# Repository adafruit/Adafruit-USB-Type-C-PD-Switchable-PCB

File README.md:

## Adafruit USB Type C Power Delivery Dummy - I2C or Switchable - HUSB238 - STEMMA QT / Qwiic PCB

<a href="http://www.adafruit.com/products/5991"><br/>
Click here to purchase one from the Adafruit shop</a>

PCB files for the Adafruit USB Type C Power Delivery Dummy - I2C or Switchable - HUSB238 - STEMMA QT / Qwiic. 

Format is EagleCAD schematic and board layout
* https://www.adafruit.com/product/5991

### Description

The HUSB238 USB PD sink chip is neat in that you can either use switches (really, resistor selection) to set the desired PD voltage or use I2C for dynamic querying and setting. We already stock a simple Adafruit USB Type C Power Delivery Dummy Breakout board around the HUSB238, but that one requires soldering closed jumpers to select the voltage. For folks who want a no-soldering-required board, this Adafruit USB Type C Power Delivery Dummy - I2C or Switchable is ready for instant gratification. No soldering required!

Compared to the basic Adafruit USB Type C Power Delivery Dummy Breakout we've done a renovation to keep the same great schematic and also add some oft-requested features:

* No soldering required! Switches allow on-the-fly voltage changes. Terminal block can be used to provide power to your robot, display, LEDs, etc.
* Green LED output lets you know that the terminal block power is on - can be disabled if you prefer
* Stemma QT for I2C control plug-and-play with Qwiic/QT
* USB Data lines available on solderable pads
* On/Off switch - you can disconnect the internal pass FET by connecting a switch between two onboard pads. When the switch is closed the output will disconnect / turn off.
* We use the HUSB328 PDL003A E-Marker variant of the chip, a little more expensive, but it can request 5A power.

It's perfect for USB Type C wall adapters providing multiple voltages. The standard offerings are 5V, 9V, 12V, 15V, 18V, and 20V. This HUSB238 breakout plugs into the USB C cable and negotiates the PD request and commands over the CC lines. For example, we can ask what voltages are available and pick the highest. Or if you need a specific voltage, it will select that one.

This breakout will be handy for projects where you need a lot more than 5V @ 2A power: this adapter can give up to 20V at 5A - yes you can get 100W over USB C! - and you could buck that down to get a ton of current at 5V or 12V if that's needed. Or use it to convert a DC or battery-powered device into a USB C powered one!

DIP switch-configured usage is simple: simply unplug the USB PD so you don't accidentally select too high a voltage for your device. Then switch ON the voltage you want: 5V, 9V, 12V, 15V, 18V, or 20V. You'll get that voltage and as much current as the adapter will provide. No microcontroller or microcomputer is required!

I2C-configured usage is also available via a Stemma QT port. Use the Arduino library and example code to query the USB Type C PD source for available voltages and currents and select the desired voltage dynamically. When configuring over I2C, the jumper settings are used on startup until the I2C commands come over.

The STEMMA QT connector lets you make solderless connections between your development board and the breakout or chain it with a wide range of other sensors and accessories using a compatible cable. QT Cable is not included, but we have a variety in the shop. 

### License

Adafruit invests time and resources providing this open source design, please support Adafruit and open-source hardware by purchasing products from [Adafruit](https://www.adafruit.com)!

Designed by Limor Fried/Ladyada for Adafruit Industries.

Creative Commons Attribution/Share-Alike, all text above must be included in any redistribution. 
See license.txt for additional details.

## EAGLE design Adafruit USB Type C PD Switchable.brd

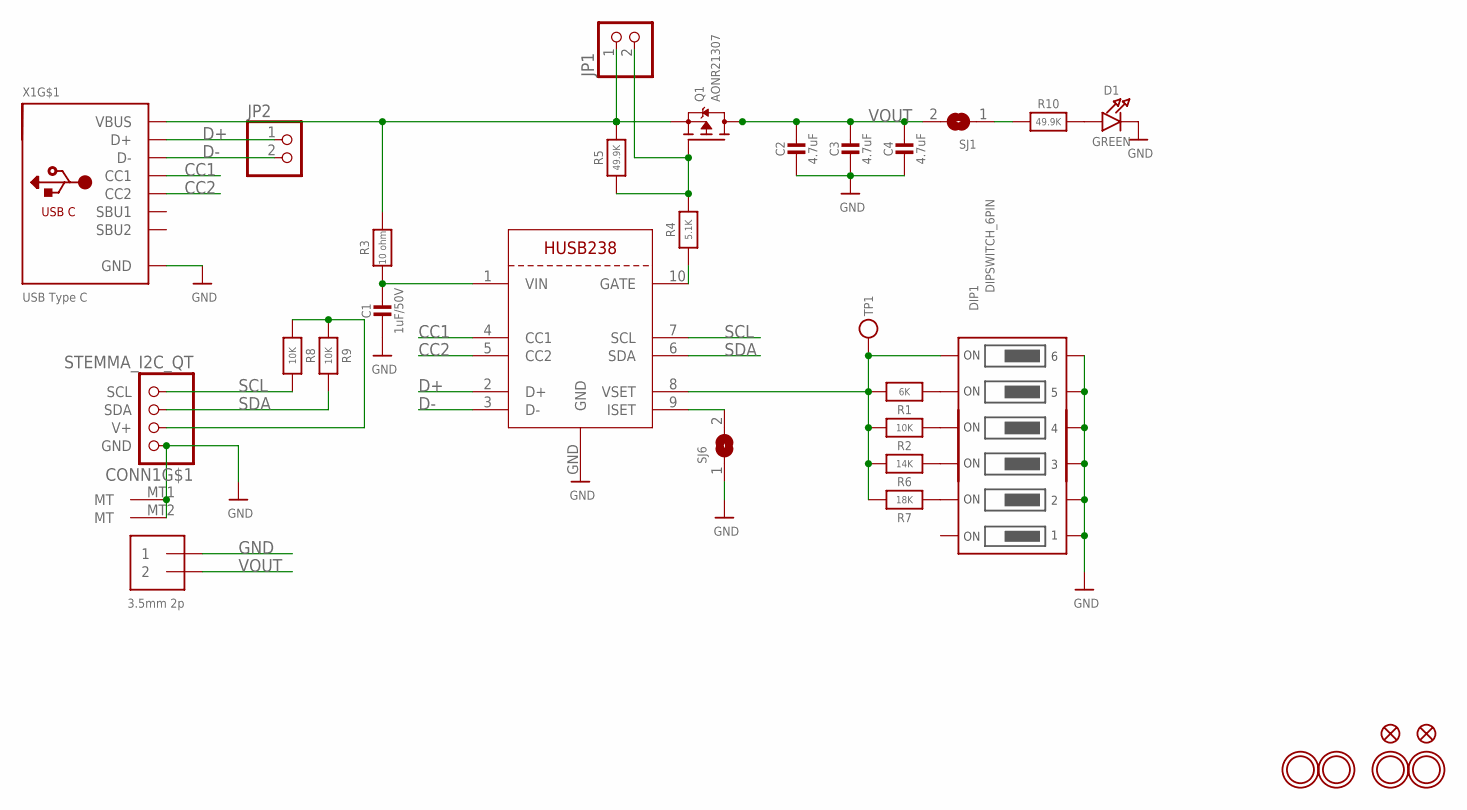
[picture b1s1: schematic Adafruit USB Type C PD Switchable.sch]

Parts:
C1: 1uF/50V; 0805-NO
C2, C3, C4: 4.7uF; 0805-NO
CONN1: STEMMA_I2C_QT; JST_SH4
D1: GREEN; CHIPLED_0603_NOOUTLINE
DIP1: DIPSWITCH_6PIN; DIPSWITCH_6PIN_1.27
FID1, FID2: FIDUCIAL_1MM
JP1, JP2: HEADER-1X2ROUND; 1X02_ROUND
Q1: AONR21307; POWERDI3333
R1: 6K; _0402NO
R2, R8, R9: 10K; _0402NO
R3: 10 ohm; _0402NO
R4: 5.1K; _0402NO
R5, R10: 49.9K; _0402NO
R6: 14K; _0402NO
R7: 18K; _0402NO
SJ1, SJ6: SOLDERJUMPERCLOSED; SOLDERJUMPER_CLOSEDWIRE
TP1: TESTPOINTROUND1.5MMNO; TESTPOINT_ROUND_1.5MM_NO
U$1, U$2, U$13, U$16: MOUNTINGHOLE2.5; MOUNTINGHOLE_2.5_PLATED
X1: USB Type C; USB_C_CUSB31-CFM2AX-01-X
X3: HUSB238; DFN10_3X3MM
X4: 3.5mm 2p; TERMBLOCK_1X2-3.5MM

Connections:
CC1: X1.A5 (CC1), X3.4 (CC1)
CC2: X1.B5 (CC2), X3.5 (CC2)
D+: JP2.1, X1.A6 (D+), X1.B6 (D+), X3.2 (D+)
D-: JP2.2, X1.A7 (D-), X1.B7 (D-), X3.3 (D-)
GND: C1.2, C2.2, C3.2, C4.2, CONN1.1 (GND), CONN1.MT1 (MT), CONN1.MT2 (MT), D1.C, DIP1.1OFF, DIP1.2OFF, DIP1.3OFF, DIP1.4OFF, DIP1.5OFF, DIP1.6OFF, SJ6.1, X1.A1B12 (GND), X1.B1A12 (GND), X3.GND, X4.1
unnamed: C1.1, R3.1, X3.1 (VIN)
unnamed: JP1.2, Q1.4 (G), R4.2, R5.2
unnamed: DIP1.6ON, R1.2, R2.2, R6.2, R7.2, TP1.P$1, X3.8 (VSET)
unnamed: R4.1, X3.10 (GATE)
unnamed: DIP1.5ON, R1.1
unnamed: DIP1.4ON, R2.1
unnamed: DIP1.3ON, R6.1
unnamed: DIP1.2ON, R7.1
unnamed: SJ6.2, X3.9 (ISET)
unnamed: CONN1.2 (V+), R8.1, R9.1
unnamed: R10.1, SJ1.1
unnamed: D1.A, R10.2
SCL: CONN1.4 (SCL), R8.2, X3.7 (SCL)
SDA: CONN1.3 (SDA), R9.2, X3.6 (SDA)
VBUS: JP1.1, Q1.1 (S), Q1.2 (S), Q1.3 (S), R3.2, R5.1, X1.A4B9 (VBUS), X1.B4A9 (VBUS)
VOUT: C2.1, C3.1, C4.1, Q1.5678 (D), SJ1.2, X4.2

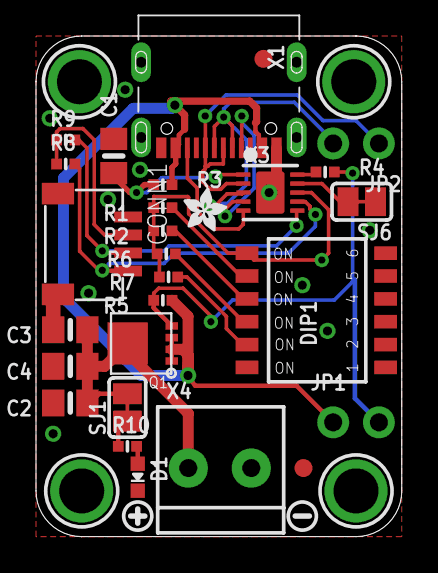
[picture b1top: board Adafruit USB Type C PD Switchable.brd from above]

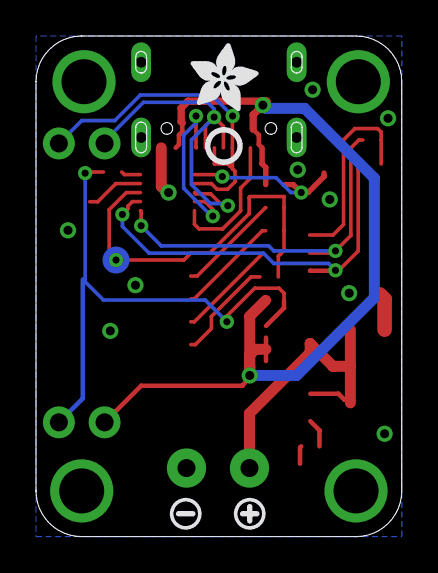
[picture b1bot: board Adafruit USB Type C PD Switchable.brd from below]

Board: 2 copper layers, 20.3 x 27.8 mm, 53 parts (10 on the bottom side), 21 nets.

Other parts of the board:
PLABEL0: PLABEL0
PLABEL1: PLABEL1
PLABEL2: PLABEL2
PLABEL3: PLABEL3
PLABEL4: PLABEL4
PLABEL5: PLABEL5
PLABEL6: PLABEL6
PLABEL7: PLABEL7
PLABEL8: PLABEL8
PLABEL9: PLABEL9
PLABEL10: PLABEL10
PLABEL11: PLABEL11
PLABEL12: PLABEL12
PLABEL13: PLABEL13
U$3: ADAFRUIT_2.5MM
U$7, U$19: SYMBOL_PLUS
U$8: PCBFEAT-REV-040
U$9: ADAFRUIT_3.5MM
U$14, U$18: SYMBOL_MINUS

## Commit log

2024-07-22 cookiecutter

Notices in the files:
parts and their libraries:
microbuilder: This work is placed in the public domain, and may be freely used for commercial and non-commercial work with the following conditions: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
